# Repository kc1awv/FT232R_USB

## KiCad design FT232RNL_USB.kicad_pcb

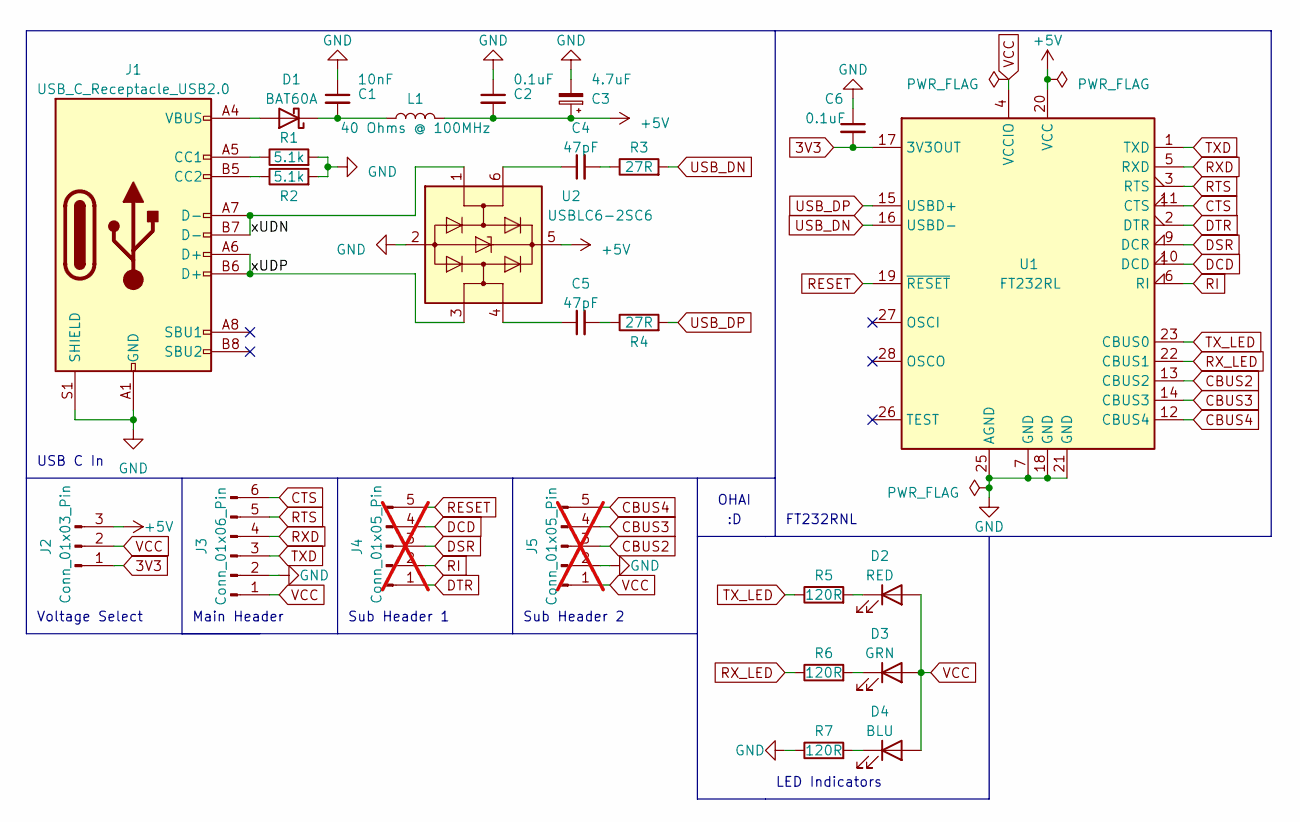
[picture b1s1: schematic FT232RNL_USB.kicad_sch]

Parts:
C1: 10nF; C_0603_1608Metric; LCSC Part # C57112
C2, C6: 0.1uF; C_0603_1608Metric; LCSC Part # C14663
C3: 4.7uF; CP_EIA-3216-18_Kemet-A; LCSC Part # C7187
C4, C5: 47pF; C_0603_1608Metric; LCSC Part # C105622
D1: BAT60A; D_SOD-323
D2: RED; LED_0603_1608Metric; LCSC Part # C84263
D3: GRN; LED_0603_1608Metric; LCSC Part # C84267
D4: BLU; LED_0603_1608Metric; LCSC Part # C84266
J1: USB_C_Receptacle_USB2.0; USB_C_Receptacle_G-Switch_GT-USB-7010ASV; LCSC Part # C2988369
J2: Conn_01x03_Pin; PinHeader_1x03_P2.54mm_Vertical
J3: Conn_01x06_Pin; PinHeader_1x06_P2.54mm_Vertical
J4, J5: Conn_01x05_Pin; PinHeader_1x05_P2.54mm_Vertical; not fitted
L1: 40 Ohms @ 100MHz; L_0603_1608Metric; LCSC Part # C142073
R1, R2: 5.1k; R_0603_1608Metric
R3, R4: 27R; R_0603_1608Metric
R5, R6, R7: 120R; R_0603_1608Metric
U1: FT232RL; SSOP-28_5.3x10.2mm_P0.65mm; LCSC Part # C8690
U2: USBLC6-2SC6; SOT-23-6; LCSC Part # C2827654

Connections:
3V3: C6.2, J2.1, U1.17 (3V3OUT)
+5V: C2.2, C3.1, J2.3, L1.2, U1.20 (VCC), U2.5 (VBUS)
/xUDN: J1.A7 (D-), J1.B7 (D-), U2.1 (I/O1)
/xUDP: J1.A6 (D+), J1.B6 (D+), U2.3 (I/O2)
CBUS2: J5.3, U1.13 (CBUS2)
CBUS3: J5.4, U1.14 (CBUS3)
CBUS4: J5.5, U1.12 (CBUS4)
CTS: J3.6, U1.11 (CTS)
DCD: J4.4, U1.10 (DCD)
DSR: J4.3, U1.9 (DCR)
DTR: J4.1, U1.2 (DTR)
GND: C1.1, C2.1, C3.2, C6.1, J1.A1 (GND), J1.A12 (GND), J1.B1 (GND), J1.B12 (GND), J1.S1 (SHIELD), J3.2, J5.2, R1.2, R2.2, R7.1, U1.7 (GND), U1.18 (GND), U1.21 (GND), U1.25 (AGND), U2.2 (GND)
unnamed: C4.1, U2.6 (I/O1)
unnamed: C4.2, R3.1
unnamed: C5.1, U2.4 (I/O2)
unnamed: C5.2, R4.1
unnamed: D1.2 (A), J1.A4 (VBUS), J1.A9 (VBUS), J1.B4 (VBUS), J1.B9 (VBUS)
unnamed: C1.2, D1.1 (K), L1.1
unnamed: D2.1 (K), R5.2
unnamed: D3.1 (K), R6.2
unnamed: D4.1 (K), R7.2
unnamed: J1.A5 (CC1), R1.1
unnamed: J1.B5 (CC2), R2.1
RESET: J4.5, U1.19 (~RESET)
RI: J4.2, U1.6 (RI)
RTS: J3.5, U1.3 (RTS)
RXD: J3.4, U1.5 (RXD)
RX_LED: R6.1, U1.22 (CBUS1)
TXD: J3.3, U1.1 (TXD)
TX_LED: R5.1, U1.23 (CBUS0)
USB_DN: R3.2, U1.16 (USBD-)
USB_DP: R4.2, U1.15 (USBD+)
VCC: D2.2 (A), D3.2 (A), D4.2 (A), J2.2, J3.1, J5.1, U1.4 (VCCIO)

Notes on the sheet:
LED Indicators
FT232RNL
Voltage Select
OHAI
Main Header
Sub Header 2
Sub Header 1
USB C In

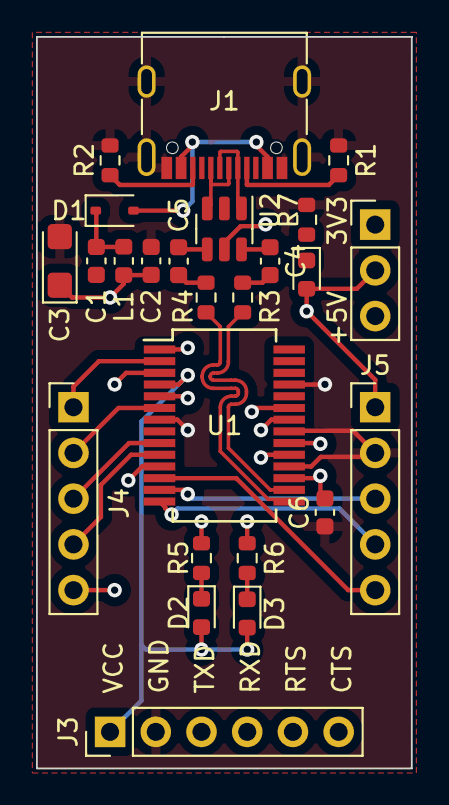
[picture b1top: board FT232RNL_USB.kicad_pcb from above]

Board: 4 copper layers, 20.8 x 40.6 mm, 25 parts (0 on the bottom side), 33 nets.
